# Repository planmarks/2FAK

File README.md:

<div align="center">

# 2FAK

**Open-source USB hardware — a FIDO2 / WebAuthn security key, and a programmable USB dongle.**

_by muru.global_

<sub>2FAK V1C — the board <em>is</em> the USB-A plug: no cable, no moving connector.</sub>

</div>

---

2FAK is a small, affordable, fully open-source USB-A board that comes in two flavours:

- **2FAK (V1C)** — a finished **FIDO2 / WebAuthn security key**, running the **Resident
  (passkey) firmware**. It is the product most people want: phishing-resistant sign-in and
  passkeys, with a secure element and a locked-down debug port.
- **Programmable 2FAK (V1A / V1B)** — the same USB-A board as an **open, reflashable dev
  platform**. It ships with ready-made **HID Injection** and **Mouse Jiggler** firmware and can
  be reprogrammed into whatever you like.

- **USB VID/PID:** `0x1209 / 0x2FA2` (0x1209 is the pid.codes open-source Vendor ID; PID 0x2FA2 is registered to us)
- **AAGUID:** `c2aa81f8-352d-56e2-c689-2bfdb5a52ccc`
- **Firmware lineage:** fork of Nitrokey FIDO2 / SoloKeys solo1 (see `NOTICE`)

### 2FAK (V1C) — the security key

The flagship security-key edition. It **ships with the ATECC608B secure element populated by
default**, and **all SWD / debug pins are closed** (RDP-2 read-out protection), so firmware and
secrets cannot be extracted or the chip reflashed over a programmer — updates are delivered as
signed images over USB. Runs the Resident (passkey) firmware: FIDO2 / WebAuthn, passkeys, and
hardware SSH keys.

2FAK (V1C) **comes with a 3D-printed case**. The 3D-printable case files are in
[`/3D Printable`](3D%20Printable).

### Programmable 2FAK (V1A / V1B)

The same STM32L442 USB-A board with its **SWD pins left open for programming and debugging** — a
blank canvas for makers. It ships with pre-made **HID Injection** and **Mouse Jiggler** firmware
and can be reflashed over an ST-Link. By default it is sold as **bare-bones hardware** (no case);
a **3D-printed case can be purchased separately**, and the 3D-printable enclosure and case files
are in [`/Programmable/3D Printable`](Programmable/3D%20Printable).

<div align="center">

<br><sub>Programmable 2FAK (V1A).</sub>
</div>

## Getting Started — 2FAK (V1C)

### As a security key (websites & apps)

1. Plug the 2FAK into a USB-A port.
2. On a site that supports security keys / passkeys, open **Settings → Security** and choose
   **add a security key** or **add a passkey**.
3. When prompted, **touch the button** on the 2FAK (and set/enter a device PIN if the site asks
   for user verification).
4. Next time you sign in, select your security key / passkey and **touch to confirm**.

Works today with Google, Microsoft, Cloudflare, Dropbox, Proton, Fastmail, Discord and more —
see [Platform compatibility](#platform-compatibility). Tip: register **two** keys (a primary and
a backup) so a lost key never locks you out.

### As a hardware SSH key

The Resident firmware doubles as a hardware-backed SSH key — the private key stays on the 2FAK
and every connection needs a touch. Both `ecdsa-sk` (ES256) and `ed25519-sk` (Ed25519) are
supported and tested (locally and against Cloudflare):

```bash
ssh-keygen -t ed25519-sk -O resident -O application=ssh:prod -f ~/.ssh/id_ed25519_sk_prod
# or -t ecdsa-sk for the ES256 key type
```

Add the resulting `.pub` to your server's `~/.ssh/authorized_keys` (or your Git host), then
`ssh` as usual and touch the key. Because the key is *resident*, you can carry it on the token
and pull it onto any machine with `ssh-keygen -K`. Add `-O verify-required` to also require the
device PIN. Requires OpenSSH 8.2+. Full sysadmin workflow (portable keys, ProxyJump bastions,
Ansible, SSH-CA, PIN tiering, Windows, backups) is in
[`Guides/2FAK Resident - Hardware SSH Key Guide.md`](Guides/2FAK%20Resident%20-%20Hardware%20SSH%20Key%20Guide.md).

## Getting Started — Programmable 2FAK

The programmable board exposes the **SWD** pads for flashing and debugging with an **ST-Link**.
You connect the ST-Link to the board's SWD pads using **pogo pins** or **male-to-male
breadboard / jumper wires**.

1. **Wire the ST-Link to the board** (see the [pin summary](#pin-summary)):

   | ST-Link | 2FAK pad |
   |---------|----------|
   | SWDIO   | PA13     |
   | SWCLK   | PA14     |
   | GND     | GND      |
   | 3.3V    | 3V3      |

   Hold the pogo pins against the pads, or solder short male-to-male wires to them.

2. **Build or grab a firmware.** Ready-made HID Injection and Mouse Jiggler images live under
   [`/Programmable/Firmware`](Programmable/Firmware) (each has its own `build.sh` and a
   `prebuilt/` image).

3. **Flash it** with STM32CubeProgrammer (ST-Link):

   ```bash
   STM32_Programmer_CLI -c port=SWD -d "Programmable/Firmware/Mouse Jiggler/prebuilt/<image>.hex" -rst
   ```

   (or use `st-flash` / OpenOCD if you prefer). Unplug the ST-Link and plug the 2FAK into a USB
   port to run the firmware.

> Because the programmable board has open SWD and no secure element, it is intended for maker /
> DIY use, not as a tamper-resistant security key. For a security key, use 2FAK (V1C).

## Hardware

<div align="center">
<table>
<tr>
<td align="center"><br><sub>Schematic (V1C)</sub></td>
<td align="center"><br><sub>PCB layout — X-ray view (V1C)</sub></td>
</tr>
</table>
</div>

### At a glance

| | |
|---|---|
| **MCU** | STM32L442KCU6 — Arm Cortex-M4F, 80 MHz, UFQFPN-32; 256 KB flash / 64 KB SRAM |
| **Secure element** | Microchip ATECC608B |
| **Interface** | USB 2.0 Full-Speed, USB-A male blade (no cable) |
| **Protocols** | FIDO2 / WebAuthn, CTAP2.0 / 2.1 / 2.3 |
| **USB ID** | 0x1209 / 0x2FA2 (pid.codes) |
| **Controls** | Tactile touch button + status LED |
| **Power** | USB bus-powered, ~30 mA, no battery |
| **Size** | ~48 × 21 mm |

<details>
<summary><strong>Full hardware details & pinout</strong></summary>

#### Microcontroller

- **Part:** STM32L442KCU6 (Arm Cortex-M4F, up to 80 MHz, UFQFPN-32). Register-compatible
  with the STM32L432.
- **Memory:** 256 KB flash, 64 KB SRAM.
- **On-chip security:** true random number generator (TRNG), AES-256 hardware accelerator,
  and flash read-out protection (RDP) supported in silicon.
- **Clocking:** crystal-less USB using the internal HSI48 oscillator with the Clock Recovery
  System (CRS); no external crystal required.

#### Secure element

- **Part:** Microchip ATECC608B, on the I2C1 bus.
- Confirmed on hardware at 7-bit I2C address 0x60, Info revision word 0x00006003 (identifies
  an ATECC608B).
- Provides tamper-resistant key storage; on fitted units it holds a device root that cannot
  be read back out of the chip. On boards where it is not fitted, the footprint remains
  unpopulated.

#### USB / UI / power / debug

- USB 2.0 **Full-Speed** (12 Mbit/s) device; **USB-A male** contacts integrated into the PCB
  edge. Dedicated ESD / TVS protection on D+, D- and VBUS.
- One **tactile push button** (user presence) and one **status LED**.
- **USB bus-powered** from 5 V, regulated on-board to 3.3 V by an LDO. ~30 mA typical, no
  battery.
- **SWD** debug/programming (SWDIO / SWCLK).

*Notice: SWD is closed in units sold as 2FAK Authentication Key.*

#### Pin summary

| Function        | Pin         |
|-----------------|-------------|
| Button          | PA0         |
| Status LED      | PB3         |
| USB D- / D+     | PA11 / PA12 |
| SWD (SWDIO/SWCLK)| PA13 / PA14|
| I2C to ATECC (SCL/SDA) | PB6 / PB7 |
| BOOT0           | PH3         |

Note: PB6 / PB7 are shared between the ATECC I2C bus and an optional debug UART. On the
populated (secure-element) boards these pins are used for the I2C bus.

</details>

## Building

Each firmware directory is self-contained. On Windows with the STM32CubeIDE toolchain, from
Git Bash:

```bash
cd "Firmware/Resident CTAP2.3"
bash build.sh                    # production-style build
```

Build switches (environment variables) are documented in `build.sh`. Artifacts land in
`prebuilt/` and are **not** committed (see [Security](#security) below).

## Security

On provisioned units the device **root secret lives in the ATECC608B secure element and never
leaves it**; per-credential keys (ES256, and Ed25519 on the Resident build) are **derived on
demand from that root and are never stored** in MCU flash (derive-and-wrap). The secure-element
path is proven on hardware and fails safe — an absent or un-provisioned chip falls back to a
software root with no behaviour change. Production units also enable **flash read-out protection
level 2 (RDP-2)**, permanently disabling the debug port, plus a **verifying bootloader** so
firmware cannot be extracted or replaced off a locked device (signed USB updates still work).

> **This is a public repository. It never contains private keys.** The following are
> git-ignored and must exist only on the build/flashing machines:
> - muru attestation private keys (`keys/2fak/ca_key.pem`, `att_key.pem`, `priv.bin/.hex`)
> - the production verifying-bootloader signing key
> - any provisioned `*.hex` (a provisioned image embeds the attestation private key)

Public certificates (root CA + leaf), the AAGUID, and the metadata statements are published
on purpose. Release firmware images are distributed via signed GitHub Releases, not committed
to the tree.

## Platform compatibility

Community/self-tested results. "not tested" simply means we haven't checked it yet.

<details>
<summary><strong>Show compatibility matrix</strong></summary>

| Platform | 2FAK Non-Resident | 2FAK Resident |
|---|---|---|
| Google | confirmed | confirmed |
| Microsoft | not supported | confirmed |
| Apple ID | not supported* | not supported* |
| Amazon | not supported | confirmed |
| Facebook / Meta | not tested | not tested |
| X | not tested | not tested |
| GitLab | not supported | confirmed |
| AWS (IAM / root) | unknown error* | unknown error* |
| Cloudflare | confirmed | confirmed |
| Okta | not tested | not tested |
| Bitwarden | not tested | not tested |
| 1Password | not tested | not tested |
| PayPal | not tested | not tested |
| Stripe | not supported | confirmed |
| Coinbase | not tested | not tested |
| Kraken | not tested | not tested |
| Binance | not tested | not tested |
| Dropbox | confirmed | confirmed |
| Proton (Mail) | confirmed | confirmed |
| Fastmail | confirmed | confirmed |
| Nextcloud | not tested | not tested |
| Discord | confirmed | confirmed |
| Salesforce | not tested | not tested |

<sub>* Apple ID and AWS entries reflect platform-side behaviour we're still investigating.</sub>

</details>

## Other firmware options

The programmable (no-secure-element) board can also run other roles. Ready-made firmware
templates — **HID Injection** and **Mouse Jiggler** — and project sources are in
[`/Programmable/Firmware`](Programmable/Firmware); each template has its own `build.sh` and a
`prebuilt/` image, and can be reflashed over an ST-Link (see
[Getting Started — Programmable 2FAK](#getting-started--programmable-2fak)).

## Compliance

2FAK is built to the **FIDO Alliance Conformance** requirements (CTAP2.0 / 2.1 / 2.3,
self-test) and is **RoHS compliant**. The conformance readiness write-ups, the RoHS declaration,
and the supporting component test data are in [`/Compliance`](Compliance) (`Compliance/FIDO` and
`Compliance/RoHS`).

## Resources

- **Resident (passkey) firmware:** [`Firmware/Resident CTAP2.3`](Firmware/Resident%20CTAP2.3)
- **Printables:** https://www.printables.com/model/1890749-2fak-v1c-enclosure
- **MakerWorld:** https://makerworld.com/en/models/3494613-2fak-v1c-case#profileId-3991427
- **2FA Key Product page:** https://shop.muru.global/2fak
- **Programmable Product page:** https://shop.muru.global/programmable-usb

## Credits

Created by **@papathought** (muru.global).

- Instagram: https://instagram.com/papathought
- Website: https://muru.global/
- Shop: https://shop.muru.global/

## License

Licensed under **Apache-2.0**. See [`LICENSE-APACHE`](LICENSE-APACHE) for the full license
text and `NOTICE` for third-party attribution.

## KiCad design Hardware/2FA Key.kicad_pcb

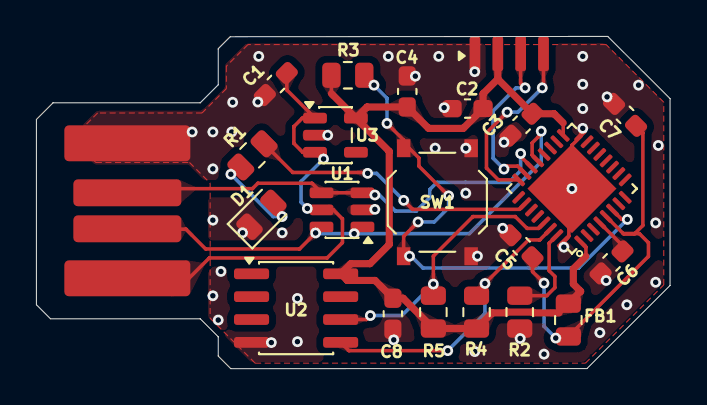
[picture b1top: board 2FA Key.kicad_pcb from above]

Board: 2 copper layers, 35.2 x 18.5 mm, 21 parts (0 on the bottom side), 13 nets.

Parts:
C1: 4.7uF; C_0603_1608Metric_Pad1.08x0.95mm_HandSolder
C2, C3: 1uF; C_0603_1608Metric_Pad1.08x0.95mm_HandSolder
C4, C5, C6, C7, C8: 100nF; C_0603_1608Metric_Pad1.08x0.95mm_HandSolder
D1: LED; LED_0805_2012Metric
FB1: FerriteBead; R_0805_2012Metric
J1: USB_A_PCB_Edge_receptacle
R1, R2: 10K; R_0805_2012Metric
R3, R4: 4.7K; R_0805_2012Metric
R5: 330; R_0805_2012Metric
SW1: Push Button; SW_Push_1P1T_XKB_TS-1187A
U1: USBLC6-2SC6; SOT-23-6
U2: ATECC608B-SSHDA; SOIC-8_3.9x4.9mm_P1.27mm
U3: AP2112K‑3.3; SOT-23-5
U4: STM32L432KCU6; QFN50P500X500X60-33N

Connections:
GND: C1.2, C2.2, C3.2, C4.2, C5.2, C6.2, C7.2, C8.2, D1.1 (K), J1.4 (GND), R2.2, SW1.1, U1.2 (GND), U2.4 (GND), U3.2 (GND), U4.16 (VSS), U4.32 (VSS), U4.33 (EXP)
J1/1-U2/1-U2/3-U4/5-C1/1: C1.1, J1.1 (VBUS), U1.5 (VBUS), U3.1 (VIN), U3.3 (EN)
J1/2-U4/1: J1.2 (D-), U1.1 (I/O1), U1.6 (I/O1), U4.21 (PA11)
J2/3-U1/4: C6.1, U4.4 (NRST)
unnamed: D1.2 (A), R1.1
R3-U1/PB3: R1.2, U4.26 (PB3/JTDO-TRACESWO)
R4-U1/PB7: R4.1, U2.5 (SDA), U4.30 (PB7)
R5-U1/PB6: R5.1, U2.6 (SCL), U4.29 (PB6)
U1/1-C3: C2.1, C3.1, C4.1, C8.1, FB1.2, R3.2, R4.2, R5.2, U2.8 (VCC), U3.5 (VOUT), U4.1 (VDD), U4.17 (VDD)
U1/5-C5-FB1: C5.1, C7.1, FB1.1, U4.5 (VDDA/VREF+)
U1/PA0-R2: R3.1, SW1.2, U4.6 (PA0/CK_IN)
U1/PH3-R1: R2.1, U4.31 (PH3/BOOT0)
U4/3-J1/3-U1/PA12: J1.3 (D+), U1.3 (I/O2), U1.4 (I/O2), U4.22 (PA12)

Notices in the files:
README.md:
License: Apache-2.0
